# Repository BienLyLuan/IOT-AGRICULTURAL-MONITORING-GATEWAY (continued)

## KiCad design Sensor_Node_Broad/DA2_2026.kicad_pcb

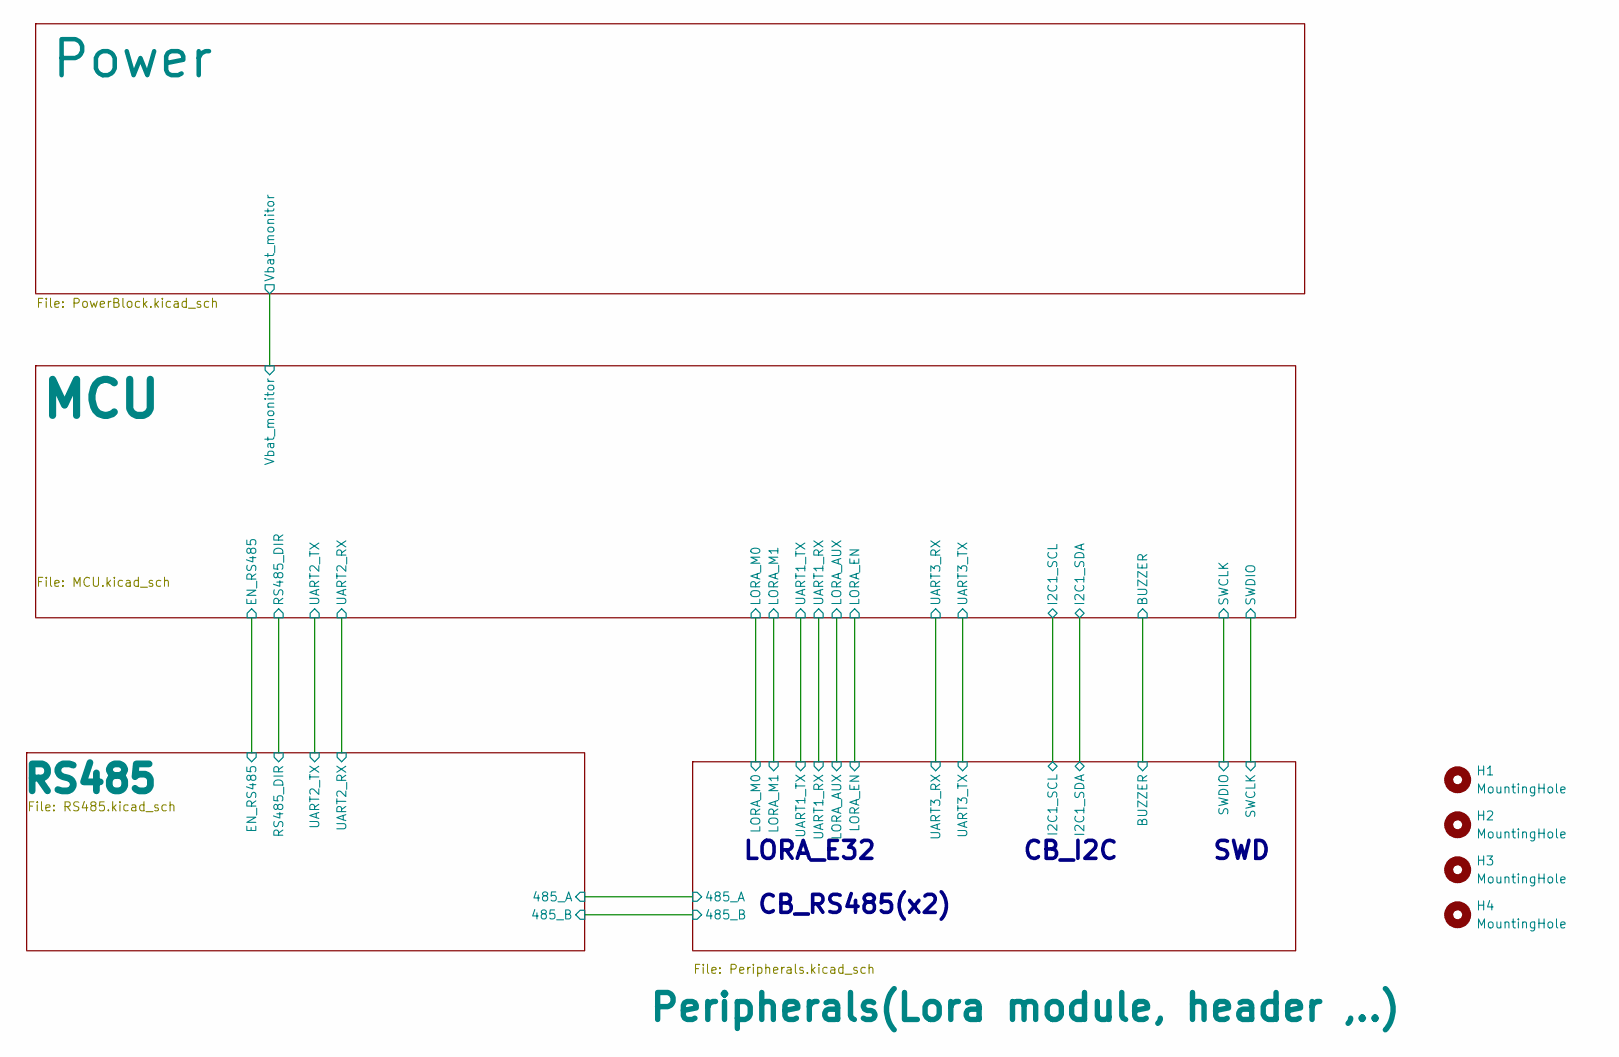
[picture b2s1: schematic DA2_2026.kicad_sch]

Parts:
H1, H2, H3, H4: MountingHole; MountingHole_3.2mm_M3_Pad_Via

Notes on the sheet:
SWD
LORA_E32
CB_RS485(x2)
CB_I2C

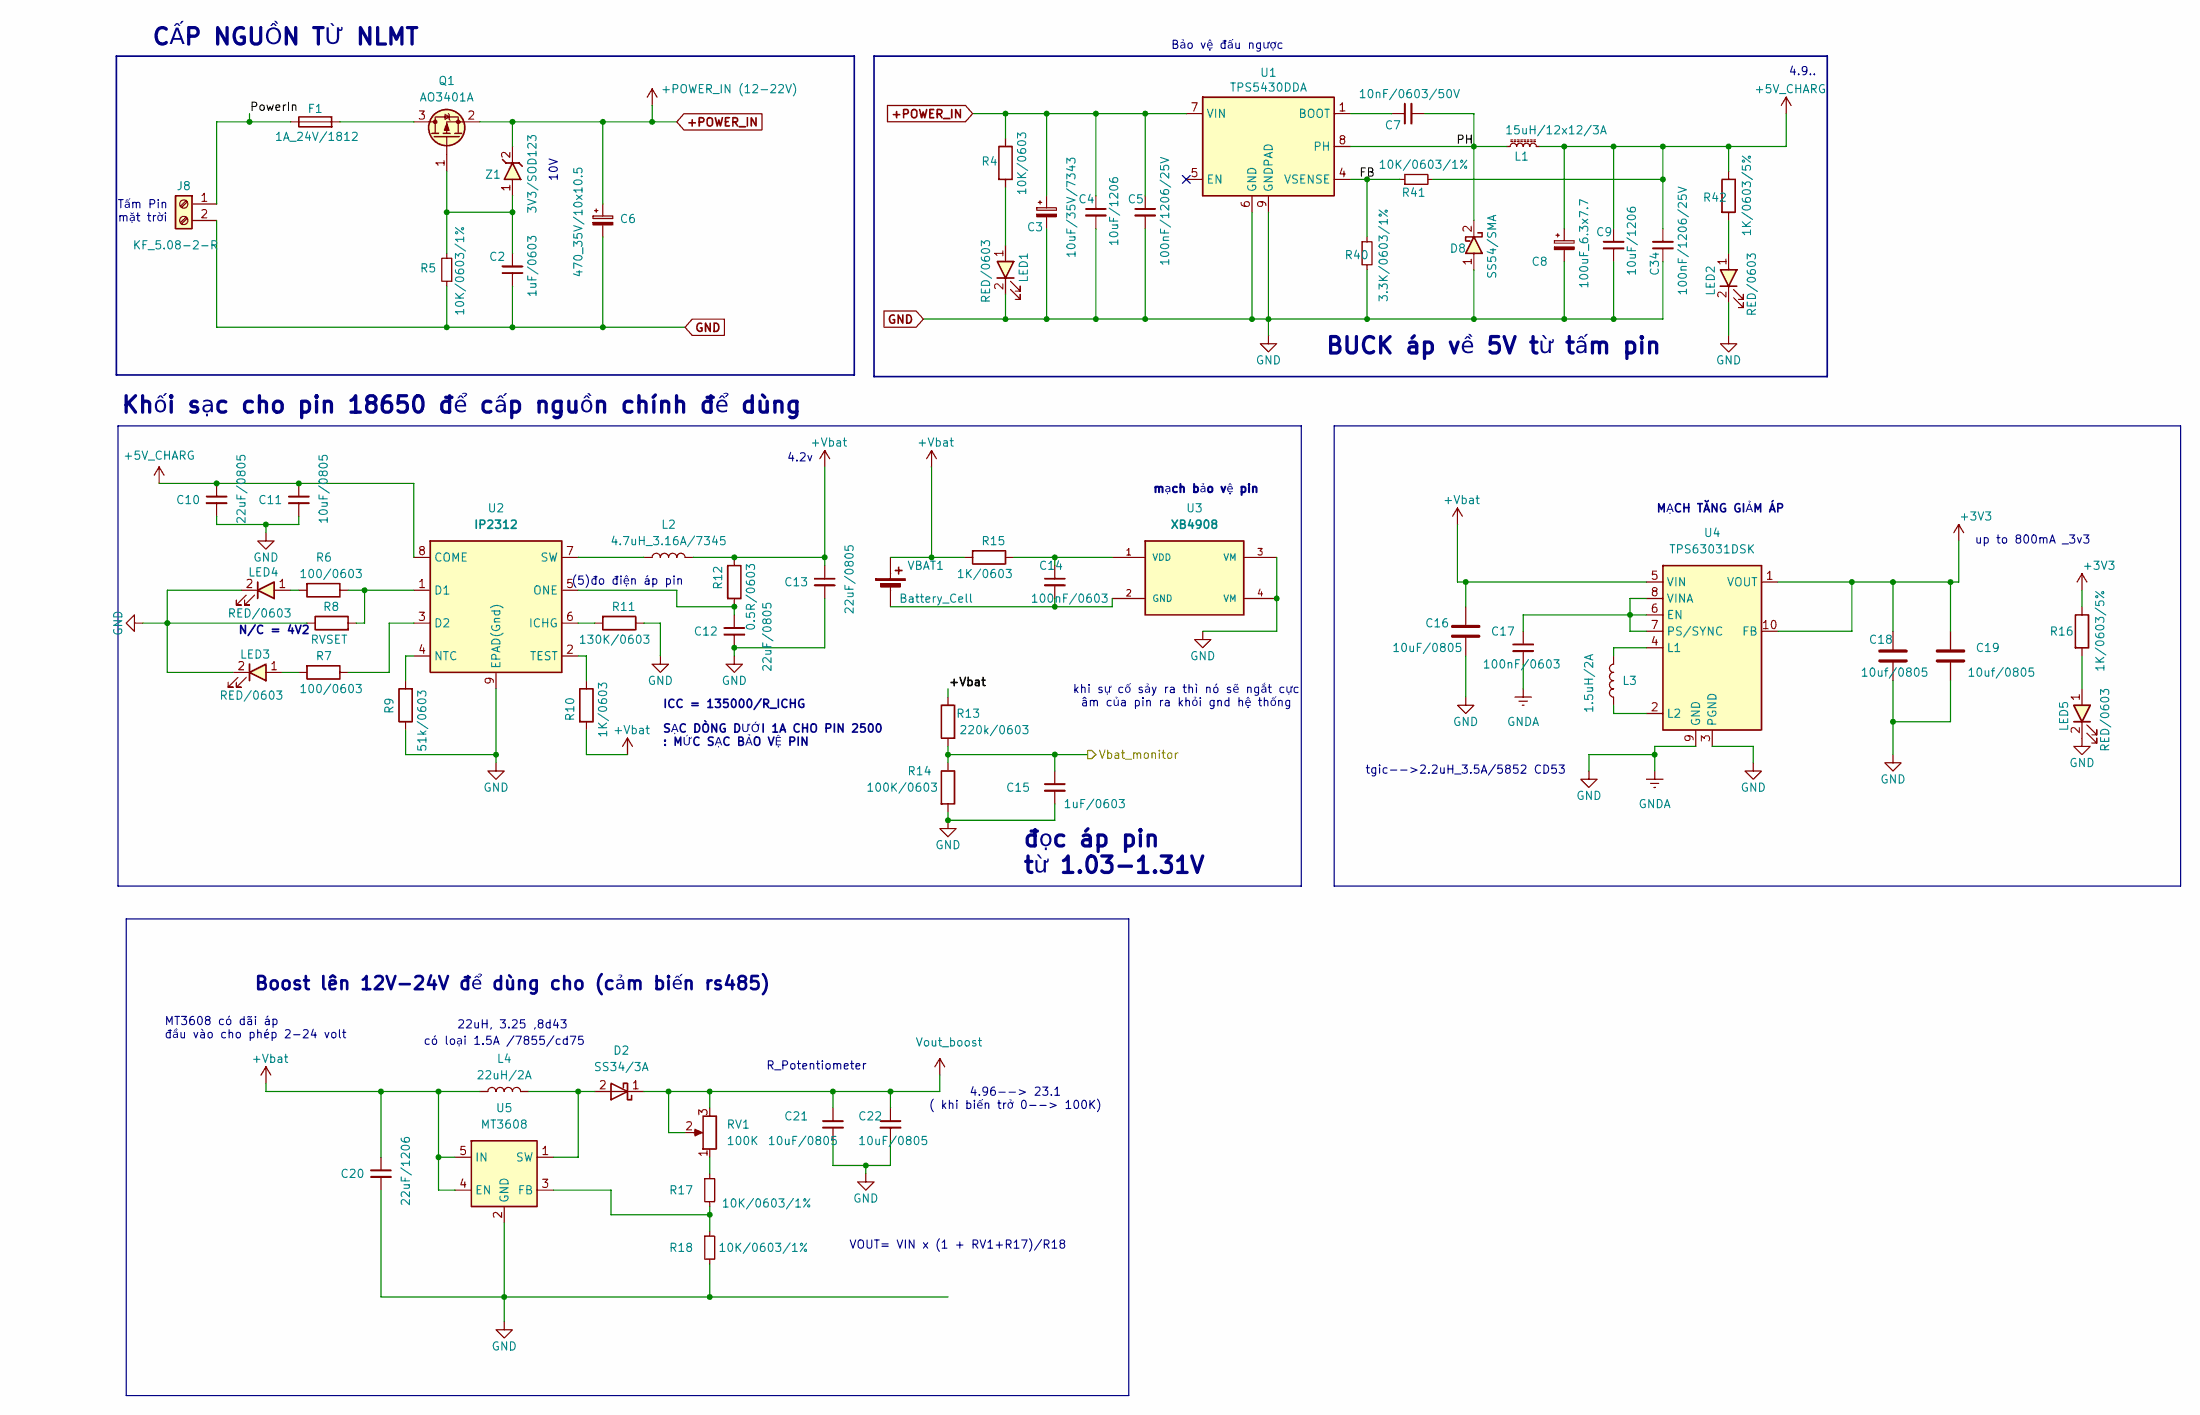
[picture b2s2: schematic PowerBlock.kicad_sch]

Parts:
C2: 1uF/0603; C_0603_1608Metric_Pad1.08x0.95mm_HandSolder
C3: 10uF/35V/7343; CP_EIA-7343-15_Kemet-W_Pad2.25x2.55mm_HandSolder; LCSC C696814
C4: 10uF/1206; C_1206_3216Metric_Pad1.33x1.80mm_HandSolder; LCSC C13585
C5, C34: 100nF/1206/25V; C_1206_3216Metric_Pad1.33x1.80mm_HandSolder; LCSC C1945
C6: 470_35V/10x10.5; CP_Elec_8x10.5
C7: 10nF/0603/50V; C_0603_1608Metric_Pad1.08x0.95mm_HandSolder; LCSC C1589
C8: 100uF_6.3x7.7; CP_Elec_6.3x7.7; LCSC C109085
C9: 10uF/1206; C_1206_3216Metric; LCSC C1849
C10, C12, C13: 22uF/0805; C_0805_2012Metric_Pad1.18x1.45mm_HandSolder; LCSC C1945
C11: 10uF/0805; C_0805_2012Metric_Pad1.18x1.45mm_HandSolder; LCSC C13585
C14, C17: 100nF/0603; C_0805_2012Metric_Pad1.18x1.45mm_HandSolder; LCSC C1945
C15: 1uF/0603; C_0603_1608Metric_Pad1.08x0.95mm_HandSolder; LCSC C1945
C16: 10uF/0805; C_0805_2012Metric_Pad1.18x1.45mm_HandSolder
C18, C19: 10uf/0805; C_0805_2012Metric_Pad1.18x1.45mm_HandSolder
C20: 22uF/1206; C_1206_3216Metric_Pad1.33x1.80mm_HandSolder; LCSC C1945
C21, C22: 10uF/0805; C_0805_2012Metric; LCSC C1945
D2: SS34/3A; D_SMA
D8: SS54/SMA; D_SMA; LCSC C22452
F1: 1A_24V/1812; Fuse_1812_4532Metric_Pad1.30x3.40mm_HandSolder
J8: KF_5.08-2-R; TerminalBlock_bornier-2_P5.08mm
L1: 15uH/12x12/3A; L_Bourns_SRR1208_12.7x12.7mm; LCSC C2929499
L2: 4.7uH_3.16A/7345; L_Wuerth_WE-PD-Typ-7345
L3: 1.5uH/2A; CD53 (5852)
L4: 22uH/2A; 8D43 (8045)
LED1, LED2, LED3, LED4, LED5: RED/0603; LED_0603_1608Metric_Pad1.05x0.95mm_HandSolder; LCSC C965799
Q1: AO3401A; SOT-23-3
R4: 10K/0603; R_0603_1608Metric_Pad0.98x0.95mm_HandSolder; LCSC C14676
R5, R41: 10K/0603/1%; R_0603_1608Metric_Pad0.98x0.95mm_HandSolder; LCSC C25804
R6, R7: 100/0603; R_0603_1608Metric_Pad0.98x0.95mm_HandSolder; LCSC C14676
R8: RVSET; R_0603_1608Metric_Pad0.98x0.95mm_HandSolder; LCSC C14676
R9: 51k/0603; R_0603_1608Metric_Pad0.98x0.95mm_HandSolder; LCSC C14676
R10, R15: 1K/0603; R_0603_1608Metric_Pad0.98x0.95mm_HandSolder; LCSC C14676
R11: 130K/0603; R_0603_1608Metric_Pad0.98x0.95mm_HandSolder; LCSC C14676
R12: 0.5R/0603; R_0603_1608Metric_Pad0.98x0.95mm_HandSolder; LCSC C14676
R13: 220k/0603; R_0603_1608Metric_Pad0.98x0.95mm_HandSolder; LCSC C14676
R14: 100K/0603; R_0603_1608Metric_Pad0.98x0.95mm_HandSolder; LCSC C14676
R16, R42: 1K/0603/5%; R_0603_1608Metric_Pad0.98x0.95mm_HandSolder; LCSC C14676
R17, R18: 10K/0603/1%; R_0603_1608Metric_Pad0.98x0.95mm_HandSolder; LCSC C22978
R40: 3.3K/0603/1%; R_0603_1608Metric_Pad0.98x0.95mm_HandSolder; LCSC C22978
RV1: 100K; Potentiometer_Bourns_3296W_Vertical
U1: TPS5430DDA; VREG_LM5017MR_NOPB; LCSC C9864
U2: IP2312; HSOP-8-1EP_3.9x4.9mm_P1.27mm_EP2.3x2.3mm
U3: XB4908; XB4908A; PARTREV 2018-09-10
U4: TPS63031DSK; WSON-10-1EP_2.5x2.5mm_P0.5mm_EP1.2x2mm
U5: MT3608; SOT-23-6
VBAT1: Battery_Cell; XH 2.54 2Pin Female
Z1: 3V3/SOD123; D_SOD-123

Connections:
+3V3: C18.1, C19.1, R16.1, U4.1 (VOUT), U4.10 (FB); also elsewhere on the board
+5V_CHARG: C8.1, C9.1, C10.1, C11.1, C34.1, L1.2, R41.2, R42.1, U2.8 (COME)
+POWER_IN: C3.1, C4.1, C5.1, C6.1, Q1.2 (S), R4.1, U1.7 (VIN), Z1.2
+Vbat: C13.1, C16.1, C20.1, L2.2, L4.1, R10.2, R12.1, R13.1, R15.2, U4.5 (VIN), U5.4 (EN), U5.5 (IN), VBAT1.1 (+); also elsewhere on the board
/MCU/Vbat_monitor: C15.1, R13.2, R14.1; also elsewhere on the board
/Power/FB: R40.1, R41.1, U1.4 (VSENSE)
/Power/PH: C7.2, D8.2, L1.1, U1.8 (PH)
/Power/PowerIn: F1.1, J8.1
GND: C2.1, C3.2, C4.2, C5.2, C6.2, C8.2, C9.2, C10.2, C11.2, C12.2, C13.2, C15.2, C16.2, C17.2, C18.2, C19.2, C20.2, C21.2, C22.2, C34.2, D8.1, J8.2, LED1.2, LED2.2, LED3.2, LED4.2, LED5.2, R5.1, R8.1, R9.1, R11.1, R14.2, R18.2, R40.2, U1.6 (GND), U1.9 (GNDPAD), U2.9 (EPAD(Gnd)), U3.3 (VM), U3.4 (VM), U4.3 (PGND), U4.9 (GND), U4.11 (PGND), U5.2 (GND); also elsewhere on the board
unnamed: D2.2 (A), L4.2, U5.1 (SW)
unnamed: LED1.1, R4.2
unnamed: LED2.1, R42.2
unnamed: LED3.1, R7.2
unnamed: LED4.1, R6.2
unnamed: LED5.1, R16.2
unnamed: F1.2, Q1.3 (D)
unnamed: C2.2, Q1.1 (G), R5.2, Z1.1
unnamed: R17.1, RV1.1
unnamed: C7.1, U1.1 (BOOT)
unnamed: R6.1, R8.2, U2.1 (D1)
unnamed: R7.1, U2.3 (D2)
unnamed: R11.2, U2.6 (ICHG)
unnamed: R9.2, U2.4 (NTC)
unnamed: C12.1, R12.2, U2.5 (ONE)
unnamed: L2.1, U2.7 (SW)
unnamed: R10.1, U2.2 (TEST)
unnamed: C14.2, U3.2 (GND), VBAT1.2 (-)
unnamed: C14.1, R15.1, U3.1 (VDD)
unnamed: C17.1, U4.6 (EN), U4.7 (PS/SYNC), U4.8 (VINA)
unnamed: L3.2, U4.4 (L1)
unnamed: L3.1, U4.2 (L2)
unnamed: R17.2, R18.1, U5.3 (FB)
Vout_boost: C21.1, C22.1, D2.1 (K), RV1.2, RV1.3; also elsewhere on the board

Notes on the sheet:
up to 800mA _3v3
CẤP NGUỒN TỪ NLMT
mạch bảo vệ pin
đọc áp pin từ 1.03-1.31V
Boost lên 12V-24V để dùng cho (cảm biến rs485)
22uH, 3.25 ,8d43
Tấm Pin mặt trời
4.2v
tgic-->2.2uH_3.5A/5852 CD53
ICC = 135000/R_ICHG
MT3608 có dãi áp đầu vào cho phép 2-24 volt
VOUT= VIN x (1 + RV1+R17)/R18
khi sự cố sảy ra thì nó sẽ ngắt cực âm của pin ra khỏi gnd hệ thống
có loại 1.5A /7855/cd75
BUCK áp về 5V từ tấm pin
10V
SẠC DÒNG DƯỚI 1A CHO PIN 2500 : MỨC SẠC BẢO VỆ PIN
R_Potentiometer
Bảo vệ đấu ngược
4.9..
N/C = 4V2
Khối sạc cho pin 18650 để cấp nguồn chính để dùng
4.96--> 23.1 ( khi biến trở 0--> 100K)
(5)đo điện áp pin
MẠCH TĂNG GIẢM ÁP

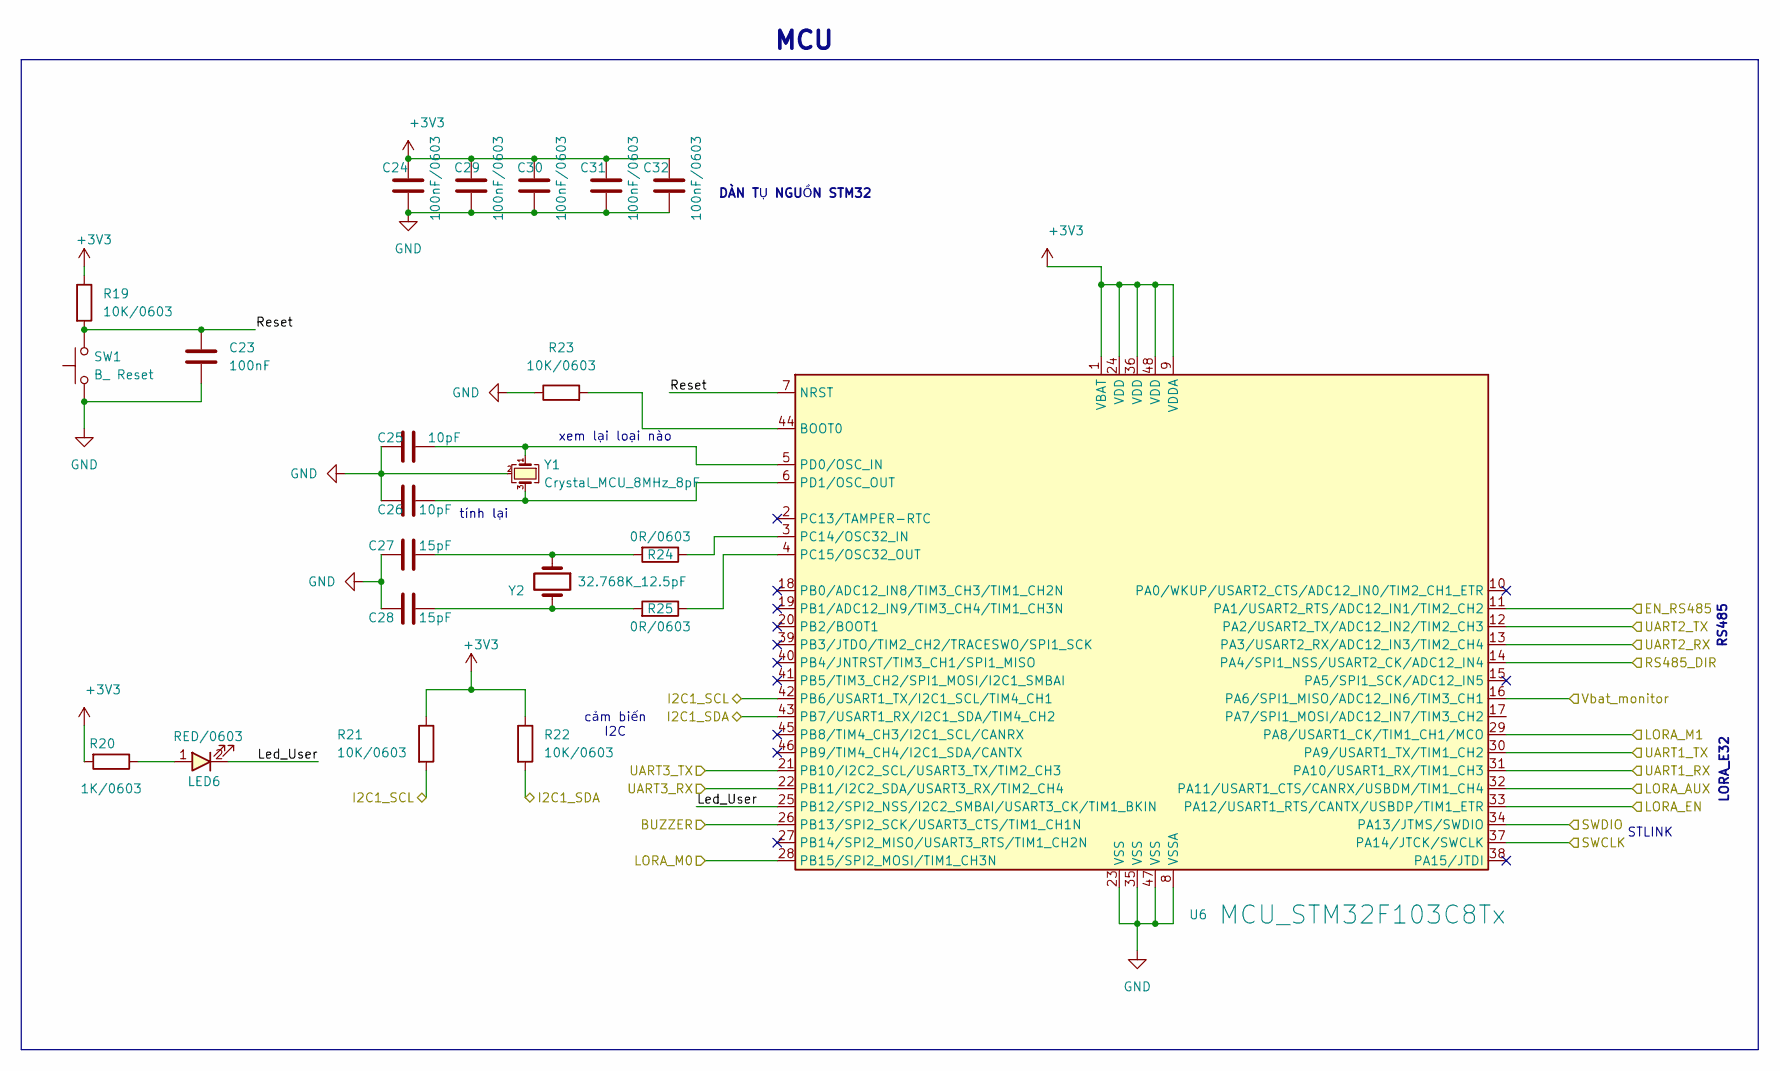
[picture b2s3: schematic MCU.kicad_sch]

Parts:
C23: 100nF; C_0603_1608Metric_Pad1.08x0.95mm_HandSolder
C24, C29, C30, C31, C32: 100nF/0603; C_0603_1608Metric_Pad1.08x0.95mm_HandSolder
C25, C26: 10pF; C_0603_1608Metric_Pad1.08x0.95mm_HandSolder
C27, C28: 15pF; C_0603_1608Metric_Pad1.08x0.95mm_HandSolder
LED6: RED/0603; LED_0603_1608Metric_Pad1.05x0.95mm_HandSolder; LCSC C965799
R19, R21, R22, R23: 10K/0603; R_0603_1608Metric_Pad0.98x0.95mm_HandSolder
R20: 1K/0603; R_0603_1608Metric_Pad0.98x0.95mm_HandSolder
R24, R25: 0R/0603; R_0603_1608Metric_Pad0.98x0.95mm_HandSolder
SW1: B_ Reset; ButtonPush-Vert-SMD-4P-SPST_PTS810
U6: MCU_STM32F103C8Tx; LQFP-48_7x7mm_P0.5mm
Y1: Crystal_MCU_8MHz_8pF; Crystal-SMD-4P-3.2x2.6mm-3225
Y2: 32.768K_12.5pF; Crystal_SMD_3215-2Pin_3.2x1.5mm

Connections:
+3V3: C24.1, C29.1, C30.1, C31.1, C32.1, R19.1, R20.2, R21.1, R22.1, U6.1 (VBAT), U6.9 (VDDA), U6.24 (VDD), U6.36 (VDD), U6.48 (VDD); also elsewhere on the board
/MCU/BUZZER: U6.26 (PB13/SPI2_SCK/USART3_CTS/TIM1_CH1N); also elsewhere on the board
/MCU/EN_RS485: U6.11 (PA1/USART2_RTS/ADC12_IN1/TIM2_CH2); also elsewhere on the board
/MCU/I2C1_SCL: R21.2, U6.42 (PB6/USART1_TX/I2C1_SCL/TIM4_CH1); also elsewhere on the board
/MCU/I2C1_SDA: R22.2, U6.43 (PB7/USART1_RX/I2C1_SDA/TIM4_CH2); also elsewhere on the board
/MCU/LORA_AUX: U6.32 (PA11/USART1_CTS/CANRX/USBDM/TIM1_CH4); also elsewhere on the board
/MCU/LORA_EN: U6.33 (PA12/USART1_RTS/CANTX/USBDP/TIM1_ETR); also elsewhere on the board
/MCU/LORA_M0: U6.28 (PB15/SPI2_MOSI/TIM1_CH3N); also elsewhere on the board
/MCU/LORA_M1: U6.29 (PA8/USART1_CK/TIM1_CH1/MCO); also elsewhere on the board
/MCU/Led_User: LED6.2, U6.25 (PB12/SPI2_NSS/I2C2_SMBAI/USART3_CK/TIM1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)
/MCU/RS485_DIR: U6.14 (PA4/SPI1_NSS/USART2_CK/ADC12_IN4); also elsewhere on the board
/MCU/Reset: C23.1, R19.2, SW1.2, U6.7 (NRST)
/MCU/SWCLK: U6.37 (PA14/JTCK/SWCLK); also elsewhere on the board
/MCU/SWDIO: U6.34 (PA13/JTMS/SWDIO); also elsewhere on the board
/MCU/UART1_RX: U6.31 (PA10/USART1_RX/TIM1_CH3); also elsewhere on the board
/MCU/UART1_TX: U6.30 (PA9/USART1_TX/TIM1_CH2); also elsewhere on the board
/MCU/UART2_RX: U6.13 (PA3/USART2_RX/ADC12_IN3/TIM2_CH4); also elsewhere on the board
/MCU/UART2_TX: U6.12 (PA2/USART2_TX/ADC12_IN2/TIM2_CH3); also elsewhere on the board
/MCU/UART3_RX: U6.22 (PB11/I2C2_SDA/USART3_RX/TIM2_CH4); also elsewhere on the board
/MCU/UART3_TX: U6.21 (PB10/I2C2_SCL/USART3_TX/TIM2_CH3); also elsewhere on the board
/MCU/Vbat_monitor: U6.16 (PA6/SPI1_MISO/ADC12_IN6/TIM3_CH1); also elsewhere on the board
GND: C23.2, C24.2, C25.1, C26.1, C27.1, C28.1, C29.2, C30.2, C31.2, C32.2, R23.1, SW1.1, U6.8 (VSSA), U6.23 (VSS), U6.35 (VSS), U6.47 (VSS), Y1.2, Y1.4; also elsewhere on the board
unnamed: C27.2, R24.2, Y2.1
unnamed: C28.2, R25.2, Y2.2
unnamed: LED6.1, R20.1
unnamed: R23.2, U6.44 (BOOT0)
unnamed: R24.1, U6.3 (PC14/OSC32_IN)
unnamed: R25.1, U6.4 (PC15/OSC32_OUT)
unnamed: C25.2, U6.5 (PD0/OSC_IN), Y1.1
unnamed: C26.2, U6.6 (PD1/OSC_OUT), Y1.3

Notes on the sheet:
STLINK
DÀN TỤ NGUỒN STM32
tính lại
LORA_E32
cảm biến I2C
xem lại loại nào
MCU
RS485

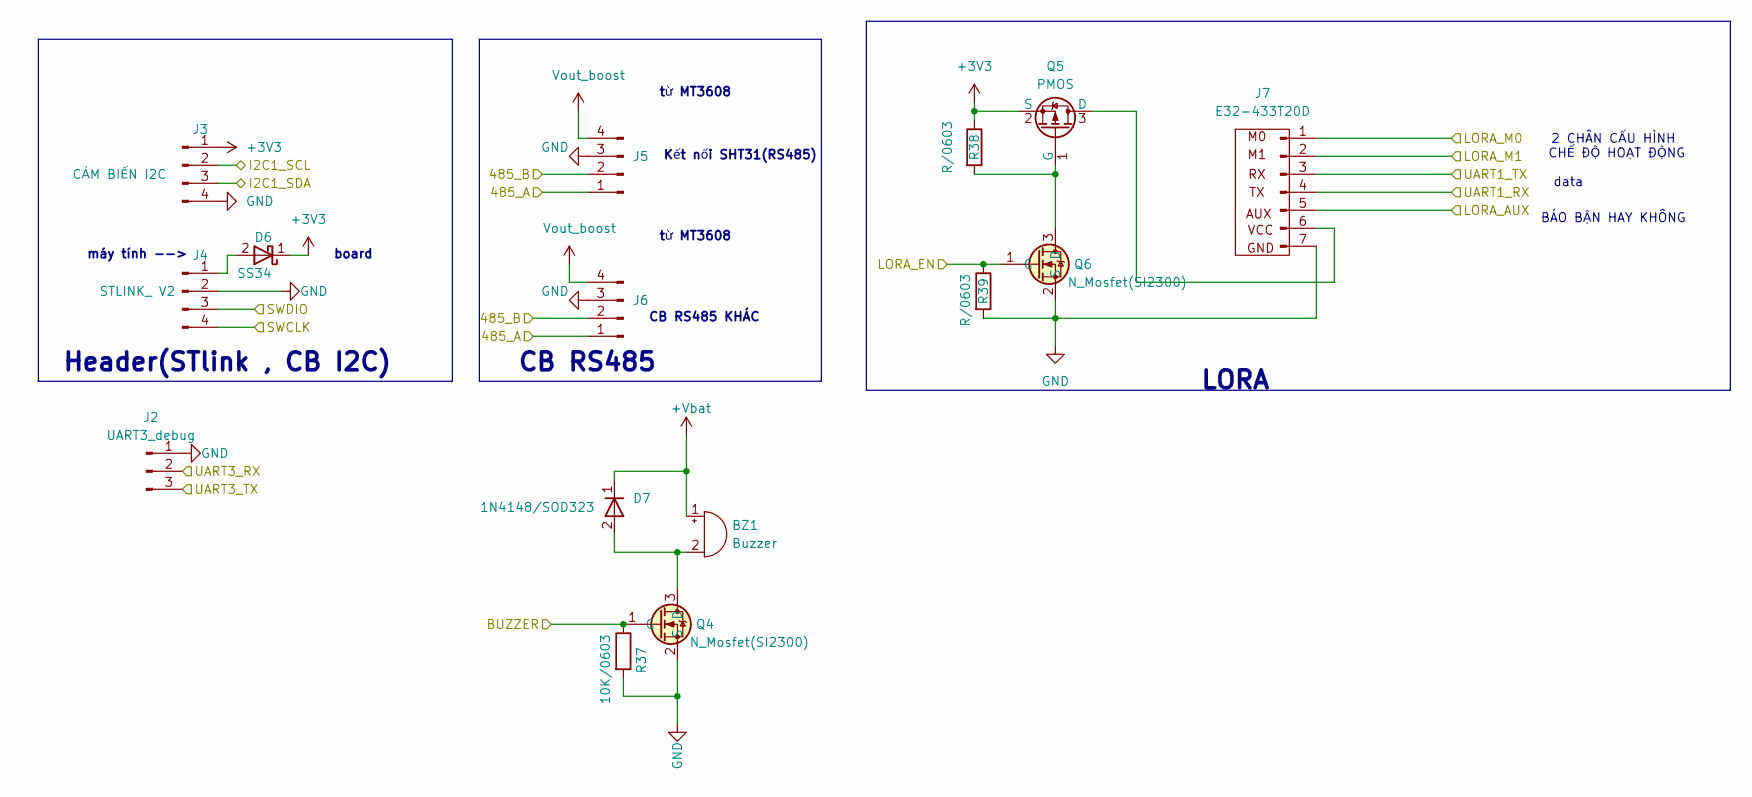
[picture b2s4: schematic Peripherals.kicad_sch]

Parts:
BZ1: Buzzer; Buzzer-THT-12x9.5_RM7.6
D6: SS34; D_SMA
D7: 1N4148/SOD323; D_SOD-323
J2: UART3_debug; PinHeader_1x03_P2.54mm_Vertical
J3: CẢM BIẾN I2C; USB_A_Molex_67643_Horizontal
J4: STLINK_ V2; PinHeader_1x04_P2.54mm_Vertical
J5, J6: Conn_01x04_Pin; TerminalBlock_bornier-4_P5.08mm
J7: E32-433T20D; lora_module
Q4, Q6: N_Mosfet(SI2300); SOT23-3
Q5: PMOS; SOT23-3
R37: 10K/0603; R_0603_1608Metric_Pad0.98x0.95mm_HandSolder
R38, R39: R/0603; R_0603_1608Metric_Pad0.98x0.95mm_HandSolder

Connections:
+3V3: D6.1 (K), J3.1, Q5.2 (S), R38.1; also elsewhere on the board
+Vbat: BZ1.1 (-), D7.1 (K); also elsewhere on the board
/MCU/BUZZER: Q4.1 (G), R37.1; also elsewhere on the board
/MCU/I2C1_SCL: J3.2; also elsewhere on the board
/MCU/I2C1_SDA: J3.3; also elsewhere on the board
/MCU/LORA_AUX: J7.5 (AUX); also elsewhere on the board
/MCU/LORA_EN: Q6.1 (G), R39.1; also elsewhere on the board
/MCU/LORA_M0: J7.1 (M0); also elsewhere on the board
/MCU/LORA_M1: J7.2 (M1); also elsewhere on the board
/MCU/SWCLK: J4.3; also elsewhere on the board
/MCU/SWDIO: J4.4; also elsewhere on the board
/MCU/UART1_RX: J7.4 (TXD); also elsewhere on the board
/MCU/UART1_TX: J7.3 (RXD); also elsewhere on the board
/MCU/UART3_RX: J2.2; also elsewhere on the board
/MCU/UART3_TX: J2.3; also elsewhere on the board
/RS485/A_IN: J5.1, J6.1; also elsewhere on the board
/RS485/B_IN: J5.2, J6.2; also elsewhere on the board
GND: J2.1, J3.4, J4.2, J5.3, J6.3, J7.7 (GND), Q4.2 (S), Q6.2 (S), R37.2, R39.2; also elsewhere on the board
unnamed: BZ1.2 (+), D7.2 (A), Q4.3 (D)
unnamed: D6.2 (A), J4.1
unnamed: J7.6 (VCC), Q5.3 (D)
unnamed: Q5.1 (G), Q6.3 (D), R38.2
Vout_boost: J5.4, J6.4; also elsewhere on the board

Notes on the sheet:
BÁO BẬN HAY KHÔNG
CB RS485 KHÁC
từ MT3608
LORA
CB RS485
2 CHÂN CẤU HÌNH CHẾ ĐỘ HOẠT ĐỘNG
Kết nối SHT31(RS485)
Header(STlink , CB I2C)
máy tính -->
board
data

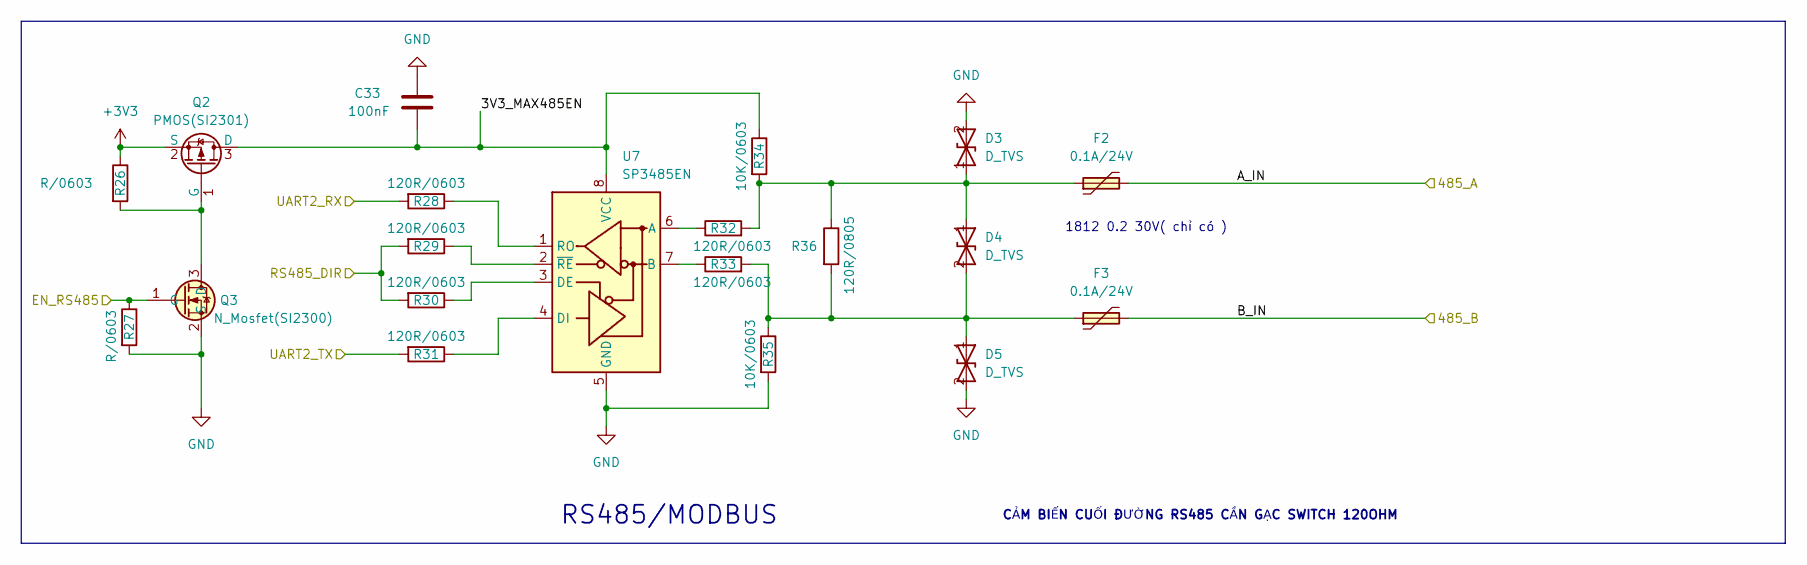
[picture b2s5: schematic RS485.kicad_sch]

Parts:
C33: 100nF; C_0603_1608Metric_Pad1.08x0.95mm_HandSolder
D3, D4, D5: D_TVS; D_SMA
F2, F3: 0.1A/24V; Fuse_1812_4532Metric_Pad1.30x3.40mm_HandSolder
Q2: PMOS(SI2301); SOT23-3
Q3: N_Mosfet(SI2300); SOT23-3
R26, R27: R/0603; R_0603_1608Metric_Pad0.98x0.95mm_HandSolder
R28, R29, R30, R31, R32, R33: 120R/0603; R_0603_1608Metric_Pad0.98x0.95mm_HandSolder
R34, R35: 10K/0603; R_0603_1608Metric_Pad0.98x0.95mm_HandSolder
R36: 120R/0805; R_0805_2012Metric_Pad1.20x1.40mm_HandSolder
U7: SP3485EN; SOIC-8_3.9x4.9mm_P1.27mm

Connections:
+3V3: Q2.2 (S), R26.1; also elsewhere on the board
/MCU/EN_RS485: Q3.1 (G), R27.1; also elsewhere on the board
/MCU/RS485_DIR: R29.2, R30.2; also elsewhere on the board
/MCU/UART2_RX: R28.2; also elsewhere on the board
/MCU/UART2_TX: R31.2; also elsewhere on the board
/RS485/3V3_MAX485EN: C33.1, Q2.3 (D), R34.1, U7.8 (VCC)
/RS485/A_IN: F2.2; also elsewhere on the board
/RS485/B_IN: F3.2; also elsewhere on the board
GND: C33.2, D3.2 (A2), D5.2 (A2), Q3.2 (S), R27.2, R35.2, U7.5 (GND); also elsewhere on the board
unnamed: D3.1 (A1), D4.1 (A1), F2.1, R32.2, R34.2, R36.1
unnamed: D4.2 (A2), D5.1 (A1), F3.1, R33.2, R35.1, R36.2
unnamed: Q2.1 (G), Q3.3 (D), R26.2
unnamed: R32.1, U7.6 (A)
unnamed: R33.1, U7.7 (B)
unnamed: R30.1, U7.3 (DE)
unnamed: R31.1, U7.4 (DI)
unnamed: R28.1, U7.1 (RO)
unnamed: R29.1, U7.2 (~RE)

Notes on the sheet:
1812 0.2 30V( chỉ có )
RS485/MODBUS
CẢM BIẾN CUỐI ĐƯỜNG RS485 CẦN GẠC SWITCH 120OHM

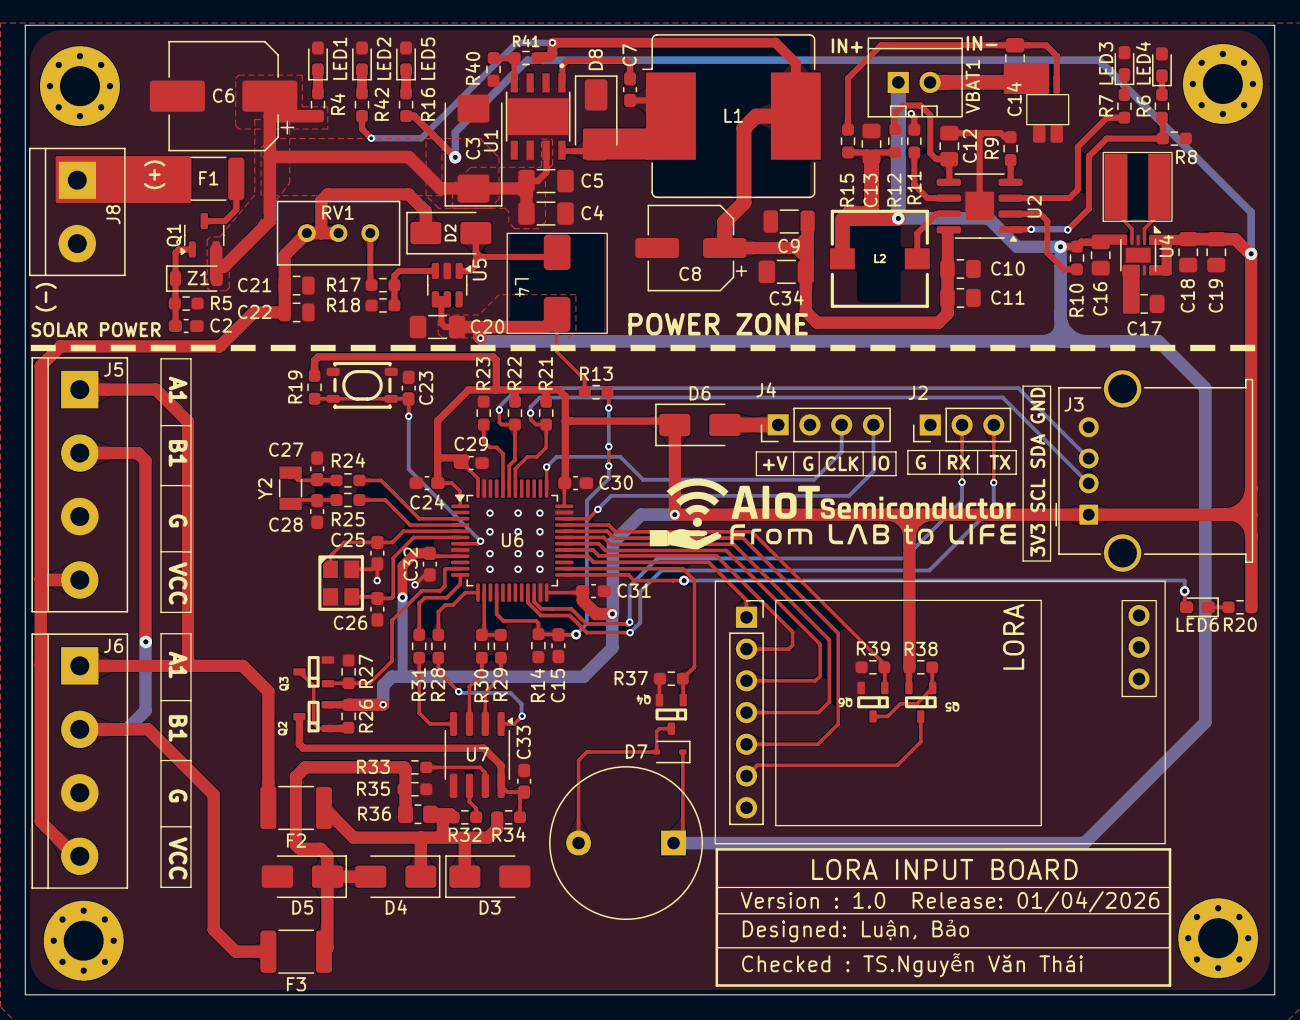
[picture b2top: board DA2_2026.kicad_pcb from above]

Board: 2 copper layers, 100.0 x 77.6 mm, 123 parts (0 on the bottom side), 76 nets.
